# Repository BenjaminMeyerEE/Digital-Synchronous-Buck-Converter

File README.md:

# Digital Synchronous Buck Converter

12 V to 6 V, 10 A synchronous buck converter with closed-loop digital control on an
STM32G474RET6. Custom 4-layer board in KiCad. The firmware runs a 400 kHz PI voltage
loop with hardware-enforced dead-time and a comparator overcurrent trip that doesn't
depend on the CPU.

<!-- TODO
     - scope captures: switching node, gate drive dead-time, load step
     - characterization numbers, then update Status
     - write up why the F.Cu pour and In2.Cu are shaped the way they are
     images are all generated, see docs/regenerate-images.md
-->

## Specifications

| Parameter | Value |
|---|---|
| Input / output | 12 V → 6 V, 10 A |
| Board | 53.1 × 50.0 mm, 4-layer |
| Controller | STM32G474RET6 (Nucleo-G474RE) |
| Switching frequency | 400 kHz (TIM1 at 170 MHz, ARR = 424) |
| Control loop | Voltage-mode PI, one update per switching period (2.5 µs) |
| Dead-time | 100 ns, hardware-enforced (TIM1 DTG = 17) |
| Current sense | INA241A3, 50 V/V into a 5 mΩ shunt, so 0.25 V/A |
| Feedback divider | 0.4047619 (ADC sees V_out × gain) |
| Sampling | Dual-simultaneous 12-bit ADC, TIM1 TRGO triggered, DMA |
| Overcurrent protection | TLV3603 comparator into TIM1 BKIN2 |
| Gate driver | UCC27211D half-bridge |

## Status

The power stage works. I've driven it from a function generator and from the test
firmware in `test-firmware/`.

Still open: the main control firmware in `firmware/` hasn't run on hardware yet, so
the closed loop is unproven. The board also hasn't been characterized, so there are
no efficiency, regulation, ripple or thermal numbers. Both are waiting on lab
access, which was shut through August 2026.

## Repository layout

| Path | Contents |
|---|---|
| `hardware/` | KiCad 10 project: schematic, PCB, design rules, library tables |
| `firmware/` | Main control firmware (CubeMX + EWARM) |
| `test-firmware/` | Standalone open-loop PWM bring-up project |
| `fabrication/` | Gerbers, BOM, pick-and-place, interactive BOM |

## Hardware

4-layer stackup with a solid internal ground plane. All four copper layers are
plotted from the top and unmirrored so they line up with each other.

| `F.Cu` — top signal + power | `In1.Cu` — ground plane |
|---|---|
|  |  |

| `In2.Cu` — power / signal | `B.Cu` — bottom signal + ground |
|---|---|
|  |  |

`B.Cu` is meant to stay as close to unbroken ground as I could keep it. It only
carries routing where a connection couldn't be finished on another layer.

Schematic: [docs/schematic.pdf](docs/schematic.pdf). Top-down render:
[docs/board-top.png](docs/board-top.png).

27 BOM lines across 49 placements. Everything in `fabrication/` comes out of the
KiCad fabrication toolkit: gerbers, a JLCPCB-format BOM and centroid file, and an
interactive HTML BOM at `fabrication/bom/ibom.html`.

## Firmware

### Control

`Buck_CtrlLoopISR()` runs at 400 kHz. It's called from a lean direct-register DMA
handler rather than going through HAL dispatch, which keeps it inside the 2.5 µs
budget. V_FB and current sense are sampled at the same instant by the dual ADC and
come back as a single 32-bit DMA word.

PI with anti-windup. Integrator and duty are both clamped to `[0, duty_limit]`, and
the clamps reject NaN so a bad value written at runtime can't reach the duty cycle.
Analog scaling uses precomputed reciprocals to keep division out of the ISR.

Gains, setpoints and the overcurrent trip level are tunable at runtime over SWD with
STM32CubeMonitor. Monitoring variables are read-only.

### Protection

Overcurrent shutdown is pure hardware: the TLV3603 comparator drives TIM1 BKIN2
directly and kills the gates in under 100 ns. It still works with the CPU halted or
hung. The software break callback only does bookkeeping, forcing MOE off, masking
the break IRQ so it can't storm, and latching the fault.

IWDG is set to 2 s, and the main loop only refreshes it while the control ISR
heartbeat is advancing. A stalled ADC or DMA path resets the board to idle instead
of leaving the half-bridge running open-loop.

TIM3 dual-edge input capture timestamps the gate edges in hardware, so the
dead-time at the power stage is measured rather than assumed.

## Test firmware

`test-firmware/` is a separate project for bringing the power stage up before
closing the loop. Open-loop complementary PWM at 400 kHz with the same 100 ns
hardware dead-time. It holds everything off for 500 ms after reset so the rails
settle and the debugger can attach, then soft-starts by walking CCR up 4 counts
every 2 ms, roughly 106 ms from 0 to 50 % duty. Kept separate so the gate drive can
be checked on its own.

## Toolchain

The CubeMX project targets EWARM V8.50. It also builds clean under
`arm-none-eabi-gcc` 14.3 (the one bundled with STM32CubeIDE 2.1.1) at
`-O2 -Wall -Wextra` with no warnings, using about 64 KB of flash and 2.4 KB of RAM.

Flash over ST-Link with STM32CubeProgrammer. CubeMonitor needs the exact `.out` ELF
matching what's on the chip, otherwise the symbol addresses won't line up.

TIM1 and IWDG are both frozen on core halt via DBGMCU, so halting in the debugger is
safe. A halt does leave the gates frozen wherever they were. The BKIN2 kill still
works while halted, but don't halt under load with the OC comparator disarmed.

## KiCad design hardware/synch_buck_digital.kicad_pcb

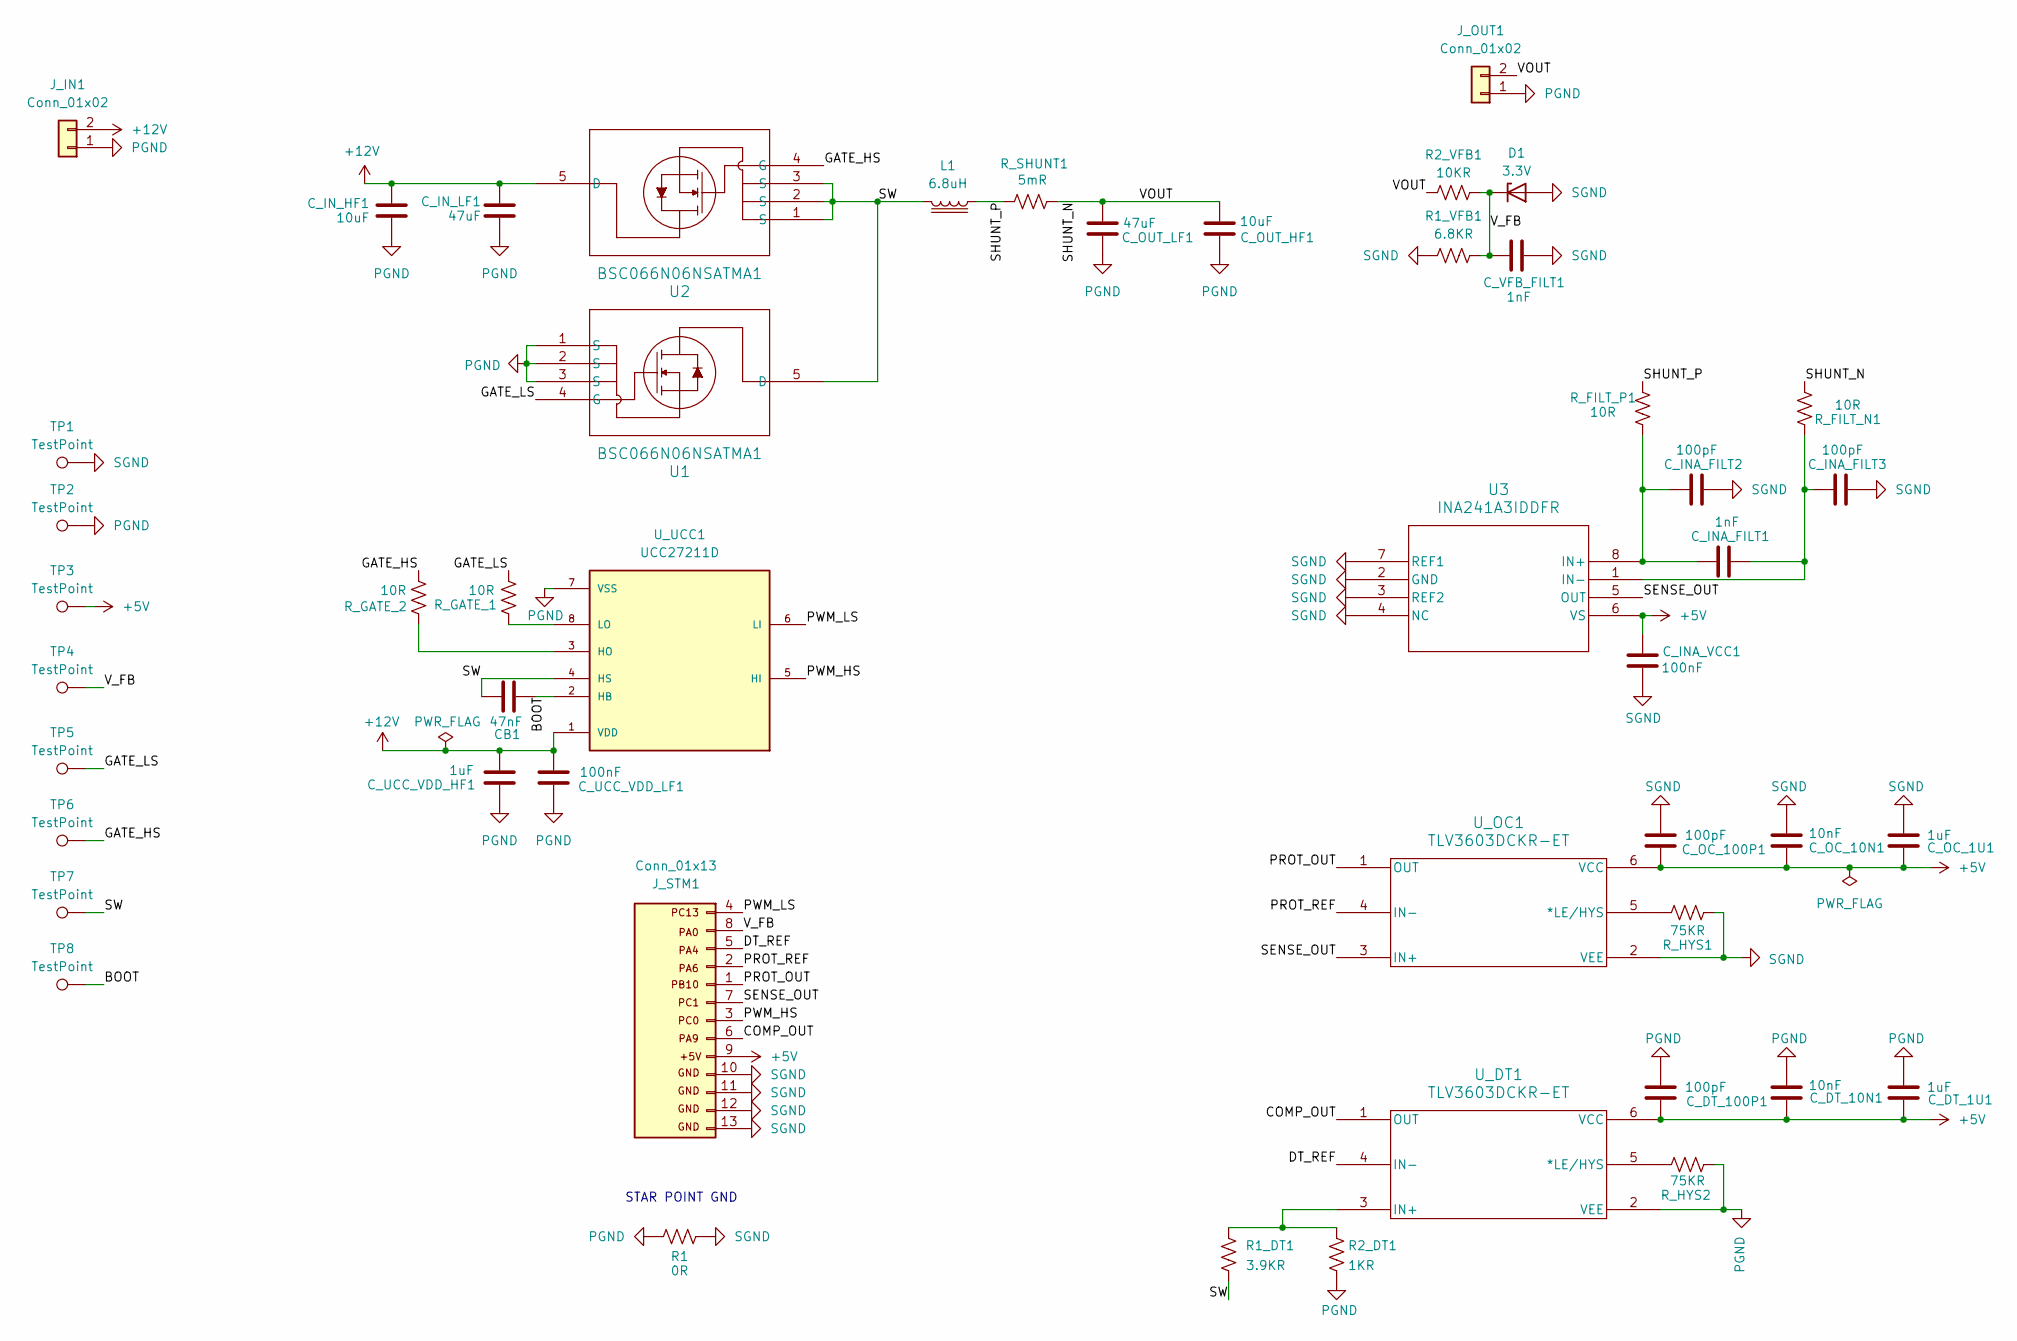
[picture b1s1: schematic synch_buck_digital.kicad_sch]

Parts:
CB1: 47nF; C_0805_2012Metric
C_DT_1U1: 1uF; C_0805_2012Metric
C_DT_10N1: 10nF; C_0402_1005Metric
C_DT_100P1: 100pF; C_0805_2012Metric
C_INA_FILT1: 1nF; C_0402_1005Metric
C_INA_FILT2, C_INA_FILT3: 100pF; C_0805_2012Metric
C_INA_VCC1: 100nF; C_0603_1608Metric
C_IN_HF1: 10uF; C_1210_3225Metric
C_IN_LF1: 47uF; CP_Elec_8x10
C_OC_1U1: 1uF; C_0805_2012Metric
C_OC_10N1: 10nF; C_0402_1005Metric
C_OC_100P1: 100pF; C_0805_2012Metric
C_OUT_HF1: 10uF; C_1210_3225Metric
C_OUT_LF1: 47uF; CP_Elec_8x10
C_UCC_VDD_HF1: 1uF; C_0805_2012Metric
C_UCC_VDD_LF1: 100nF; C_0603_1608Metric
C_VFB_FILT1: 1nF; C_0603_1608Metric
D1: 3.3V; D_SOD-123
J_IN1: Conn_01x02; TerminalBlock_MaiXu_MX126-5.0-02P_1x02_P5.00mm
J_OUT1: Conn_01x02; TerminalBlock_MaiXu_MX126-5.0-02P_1x02_P5.00mm
J_STM1: Conn_01x13; PinHeader_1x13_P2.54mm_Vertical
L1: 6.8uH; L_Coilcraft_XAL1010-XXX
R1: 0R
R1_DT1: 3.9KR; R_0603_1608Metric
R1_VFB1: 6.8KR; R_0603_1608Metric
R2_DT1: 1KR; R_0603_1608Metric
R2_VFB1: 10KR; R_0603_1608Metric
R_FILT_N1: 10R; R_0402_1005Metric
R_FILT_P1: 10R; R_0402_1005Metric
R_GATE_1, R_GATE_2: 10R; C_0805_2012Metric
R_HYS1, R_HYS2: 75KR; R_0603_1608Metric
R_SHUNT1: 5mR; RES_2012_SUS
TP1, TP2, TP3, TP4, TP5, TP6, TP7, TP8: TestPoint; TestPoint_Pad_2.0x2.0mm
U1, U2: BSC066N06NSATMA1; Infineon_PG-TDSON-8_6.15x5.15mm
U3: INA241A3IDDFR; SOT23-8_DDF_TEX
U_DT1: TLV3603DCKR-ET; SC70_DCK_TEX
U_OC1: TLV3603DCKR-ET; SC70_DCK_TEX
U_UCC1: UCC27211D; SOIC127P599X175-8N; PARTREV F

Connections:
+5V: C_DT_1U1.1, C_DT_10N1.1, C_DT_100P1.1, C_INA_VCC1.1, C_OC_1U1.1, C_OC_10N1.1, C_OC_100P1.1, J_STM1.9, TP3.1 (1_1), U3.6 (VS), U_DT1.6 (VCC), U_OC1.6 (VCC)
+12V: C_IN_HF1.1, C_IN_LF1.1, C_UCC_VDD_HF1.2, C_UCC_VDD_LF1.2, J_IN1.2, U2.5 (D), U_UCC1.1 (VDD)
/BOOT: CB1.1, TP8.1 (1_1), U_UCC1.2 (HB)
/COMP_OUT: J_STM1.6 (Pin_8), U_DT1.1 (OUT)
/DT_REF: J_STM1.5 (Pin_3), U_DT1.4 (IN-)
/GATE_HS: R_GATE_2.1, TP6.1 (1_1), U2.4 (G)
/GATE_LS: R_GATE_1.2, TP5.1 (1_1), U1.4 (G)
/PROT_OUT: J_STM1.1 (Pin_5), U_OC1.1 (OUT)
/PROT_REF: J_STM1.2 (Pin_4), U_OC1.4 (IN-)
/PWM_HS: J_STM1.3 (Pin_7), U_UCC1.5 (HI)
/PWM_LS: J_STM1.4 (Pin_1), U_UCC1.6 (LI)
/SENSE_OUT: J_STM1.7 (Pin_6), U3.5 (OUT), U_OC1.3 (IN+)
/SHUNT_N: C_OUT_HF1.1, C_OUT_LF1.1, J_OUT1.2, R2_VFB1.1, R_FILT_N1.2, R_SHUNT1.2
/SHUNT_P: L1.1, R_FILT_P1.1, R_SHUNT1.1
/SW: CB1.2, L1.2, R1_DT1.2, TP7.1 (1_1), U1.5 (D), U2.1 (S), U2.2 (S), U2.3 (S), U_UCC1.4 (HS)
/V_FB: C_VFB_FILT1.2, D1.1 (K), J_STM1.8 (Pin_2), R1_VFB1.2, R2_VFB1.2, TP4.1 (1_1)
unnamed: C_INA_FILT1.2, C_INA_FILT2.2, R_FILT_P1.2, U3.8 (IN+)
unnamed: C_INA_FILT1.1, C_INA_FILT3.2, R_FILT_N1.1, U3.1 (IN-)
unnamed: R_HYS2.2, U_DT1.5 (*LE/HYS)
unnamed: R1_DT1.1, R2_DT1.2, U_DT1.3 (IN+)
unnamed: R_HYS1.2, U_OC1.5 (*LE/HYS)
unnamed: R_GATE_2.2, U_UCC1.3 (HO)
unnamed: R_GATE_1.1, U_UCC1.8 (LO)
PGND: C_DT_1U1.2, C_DT_10N1.2, C_DT_100P1.2, C_IN_HF1.2, C_IN_LF1.2, C_OUT_HF1.2, C_OUT_LF1.2, C_UCC_VDD_HF1.1, C_UCC_VDD_LF1.1, J_IN1.1, J_OUT1.1, R1.1, R2_DT1.1, R_HYS2.1, TP2.1 (1_1), U1.1 (S), U1.2 (S), U1.3 (S), U_DT1.2 (VEE), U_UCC1.7 (VSS)
SGND: C_INA_FILT2.1, C_INA_FILT3.1, C_INA_VCC1.2, C_OC_1U1.2, C_OC_10N1.2, C_OC_100P1.2, C_VFB_FILT1.1, D1.2 (A), J_STM1.10, J_STM1.11, J_STM1.12, J_STM1.13, R1.2, R1_VFB1.1, R_HYS1.1, TP1.1 (1_1), U3.2 (GND), U3.3 (REF2), U3.4 (NC), U3.7 (REF1), U_OC1.2 (VEE)

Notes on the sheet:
STAR POINT GND

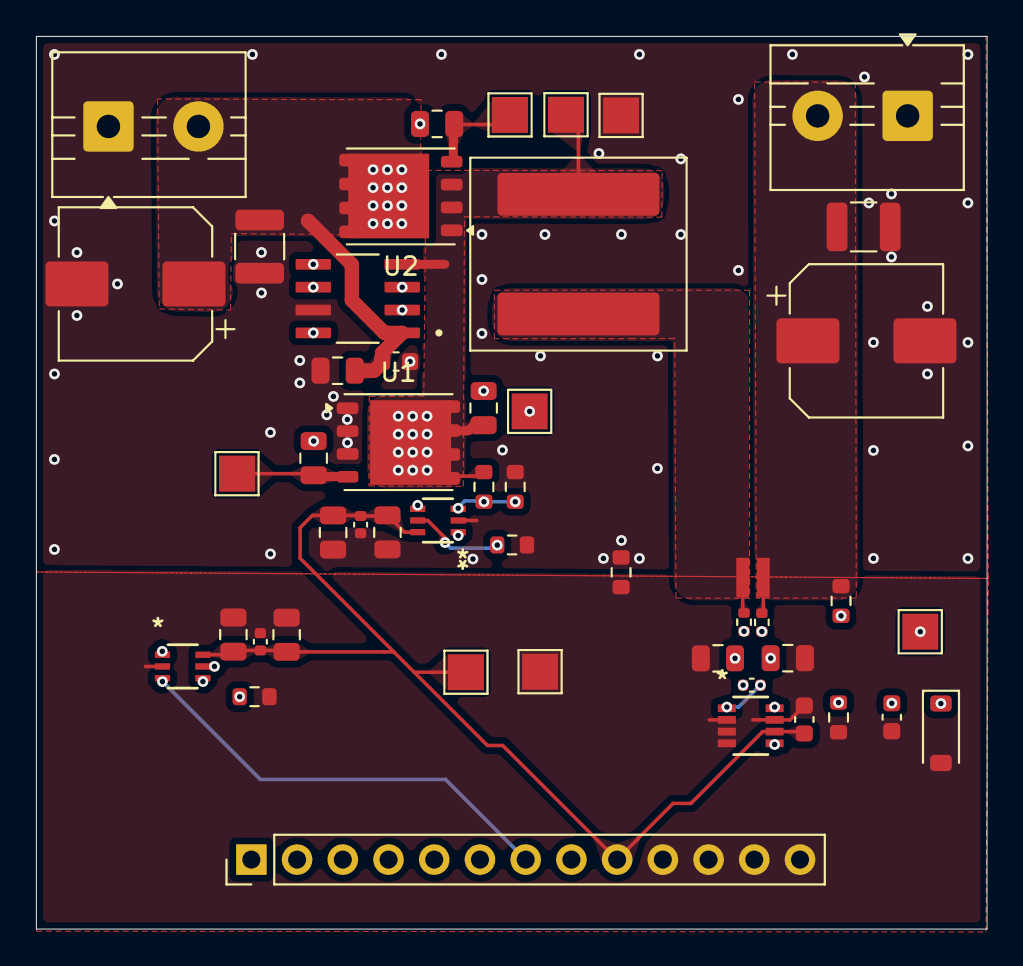
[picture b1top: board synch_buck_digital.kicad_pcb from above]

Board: 4 copper layers, 52.8 x 49.6 mm, 49 parts (0 on the bottom side), 25 nets.

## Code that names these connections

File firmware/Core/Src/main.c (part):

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/* --- Analog scaling (precomputed reciprocals: no division in the ISR) ------ */
#define ADC_VREF_V              3.3f
#define ADC_FULL_SCALE          4095.0f
#define VFB_DIVIDER_GAIN        0.4047619f  /* V_FB divider: ADC sees Vout * this         */
#define CURR_SENSE_V_PER_A      0.25f       /* INA241A3 gain 50 x 5 mOhm shunt            */
#define ADC_RAW_TO_VOUT_V       ((ADC_VREF_V / ADC_FULL_SCALE) / VFB_DIVIDER_GAIN)   /* ~1.9910e-3 V/LSB */
#define ADC_RAW_TO_AMPS         ((ADC_VREF_V / ADC_FULL_SCALE) / CURR_SENSE_V_PER_A) /* ~3.2234e-3 A/LSB */
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/* --- Limits / interlocks ---------------------------------------------------- */
#define OC_TRIP_MIN_A           0.5f        /* start refused while set_oc_trip_A < this   */
#define DUTY_MAX_ABS            0.98f       /* absolute ceiling for set_duty_max          */
#define VOUT_SET_MAX_V          8.0f        /* V_FB divider saturates the ADC at ~8.15 V  */
#define SOFTSTART_MS_MIN        1.0f        /* also guards the ramp-increment division    */
#define SOFTSTART_MS_MAX        10000.0f

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volatile float    mon_pwm_ls_duty_pct    = 0.0f;           /* low-side effective duty [%]            */
volatile uint8_t  mon_pwm_hs_active      = 0u;             /* 1 = MOE on and HS switching            */
volatile uint8_t  mon_pwm_ls_active      = 0u;             /* 1 = MOE on (LS driven)                 */
volatile uint8_t  mon_prot_out_state     = 0u;             /* live PROT_OUT pin level (PA11)         */
volatile uint8_t  mon_dt_out_state       = 0u;             /* live DT_OUT comparator level (PB4)     */
volatile uint32_t mon_dt_edge_count      = 0u;             /* total DT_OUT edges captured by TIM3    */
volatile uint32_t mon_dt_pulse_width_ns  = 0u;             /* last DT_OUT high-pulse width [ns]      */
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  }

  /* --- DAC comparator references: start and apply the power-on defaults.
         PROT_REF (DAC1_OUT1/PA4) from set_oc_trip_A (default 0 A = disarmed),
         DT_REF   (DAC2_OUT1/PA6) from set_dt_ref_A  (default 0.1 A).        */
  if (HAL_DAC_Start(&hdac1, DAC_CHANNEL_1) != HAL_OK)
  {
    Error_Handler();
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  while (1)
  {
    /* --- live pin monitors (GPIO input path is valid even in AF mode) ------ */
    mon_prot_out_state = (uint8_t)((GPIOA->IDR >> 11) & 1u); /* PA11 = PROT_OUT / TIM1_BKIN2 */
    mon_dt_out_state   = (uint8_t)((GPIOB->IDR >> 4) & 1u);  /* PB4  = DT_OUT (this poll is the single owner) */

    /* --- tunable sanitation + DAC reference updates ------------------------ */
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  {
    counts = (uint32_t)(trip * AMPS_TO_DAC_COUNTS + 0.5f);
    if (counts > 4095u) { counts = 4095u; }
    (void)HAL_DAC_SetValue(&hdac1, DAC_CHANNEL_1, DAC_ALIGN_12B_R, counts); /* PROT_REF, PA4 */
    dac_oc_applied_A = trip;
  }

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  {
    counts = (uint32_t)(trip * AMPS_TO_DAC_COUNTS + 0.5f);
    if (counts > 4095u) { counts = 4095u; }
    (void)HAL_DAC_SetValue(&hdac2, DAC_CHANNEL_1, DAC_ALIGN_12B_R, counts); /* DT_REF, PA6 */
    dac_dt_applied_A = trip;
  }
}
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
/**
  * @brief  Explicit FAULT -> IDLE transition (fault-clear path only).
  *         The gate condition reads the live PROT_OUT level (PA11) directly
  *         from GPIOA->IDR at the decision point, inside the critical section:
  *         clearing is refused while the OC comparator output is still high.
  *         Pending break flags are cleared and the break interrupt source is
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  *           - state is still IDLE (a BRK2 event racing this call wins),
  *           - no break flag is pending in TIM1->SR (a BRK2 pulse latched as a
  *             pended ISR must run its callback, not be overtaken by MOE on),
  *           - the live PROT_OUT level (PA11) is low right now.
  */
static void app_arm_soft_start(void)
{
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}

/**
  * @brief  TIM1 BRK2 event (BKIN2 = PA11 = PROT_OUT, overcurrent comparator,
  *         active high). Hardware clears MOE on the break event, but that is
  *         NOT sufficient here: a BRK2 pulse can be latched as a pended ISR
  *         while the arming path's software MOE-enable executes AFTER the
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
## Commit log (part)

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2026-04-21 first setup
2026-04-21 *.bak *.bck *-backups/ .history/ *.kicad_pcb-bak *.kicad_sch-bak fabrication/ production/ jlcpcb/ gerbers/ bom/ pos/ *.zip .DS_Store Thumbs.db desktop.ini Please enter the commit message for your cha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
2026-04-21 Fixed .gitignore
2026-04-21 Remove ignored files from tracking
2026-04-22 pouring topology started
2026-04-22 Smaller SW Pour
2026-04-26 Updated pcb
2026-04-27 Updated pour topology
2026-04-28 Signal Traces Added
2026-04-28 More Traces
2026-04-28 Fixed FET Footprint and updated pour topology
2026-04-28 pcb finished
2026-04-28 shrunk SW pour
2026-04-28 Reduced board size
2026-04-29 Small Layout Change
2026-04-30 Small Changes
2026-05-12 Added stitching and thermal pours
2026-05-18 Small fix
2026-05-18 Small layout fix
2026-05-28 V1 finished. Final touchups to schematic planned
2026-06-01 Minor clean up
2026-06-01 fixed gitignore

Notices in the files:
firmware/Core/Src/main.c:
Copyright (c) 2026 STMicroelectronics.
All rights reserved.
This software is licensed under terms that can be found in the LICENSE file
